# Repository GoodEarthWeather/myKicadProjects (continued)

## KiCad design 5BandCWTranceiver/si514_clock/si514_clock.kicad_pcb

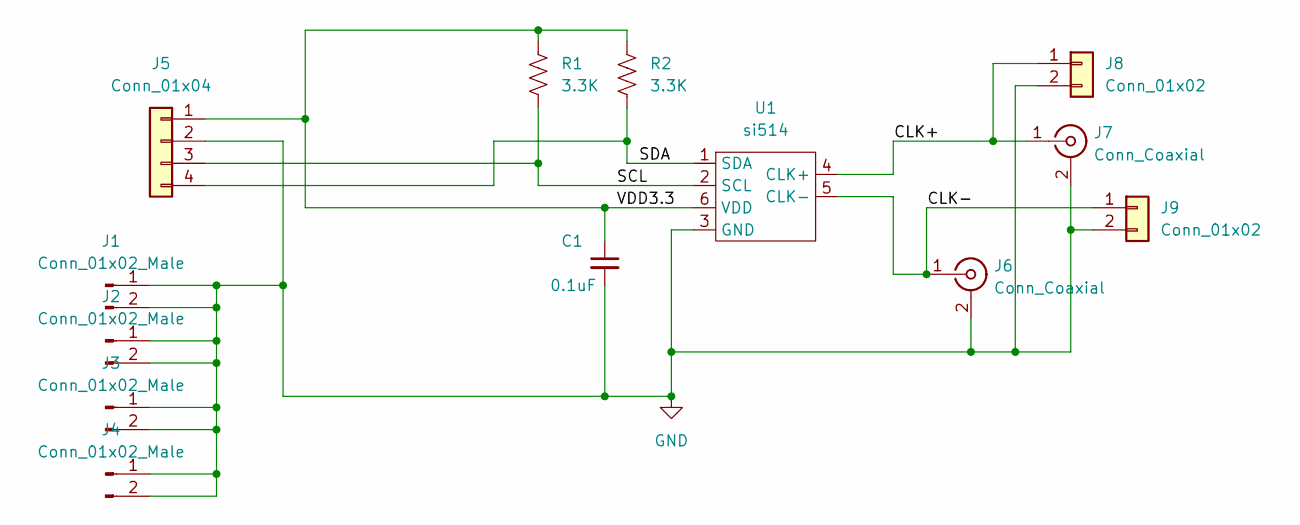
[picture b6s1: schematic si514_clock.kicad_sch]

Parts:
C1: 0.1uF; C_0603_1608Metric_Pad1.08x0.95mm_HandSolder
J1, J2, J3, J4: Conn_01x02_Male; PinHeader_1x02_P2.54mm_Vertical
J5: Conn_01x04; PinHeader_1x04_P2.54mm_Vertical
J6, J7: Conn_Coaxial; SMA_Samtec_SMA-J-P-X-ST-EM1_EdgeMount
J8, J9: Conn_01x02; PinHeader_1x02_P2.54mm_Vertical
R1, R2: 3.3K; R_0603_1608Metric_Pad0.98x0.95mm_HandSolder
U1: si514; si514_3.2x5

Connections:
/CLK+: J7.1 (In), J8.1, U1.4 (CLK+)
/CLK-: J6.1 (In), J9.1, U1.5 (CLK-)
/SCL: J5.3, R1.2, U1.2 (SCL)
/SDA: J5.4, R2.2, U1.1 (SDA)
/VDD3.3: C1.1, J5.1, R1.1, R2.1, U1.6 (VDD)
GND: C1.2, J1.1, J1.2, J2.1, J2.2, J3.1, J3.2, J4.1, J4.2, J5.2, J6.2 (Ext), J7.2 (Ext), J8.2, J9.2, U1.3 (GND)

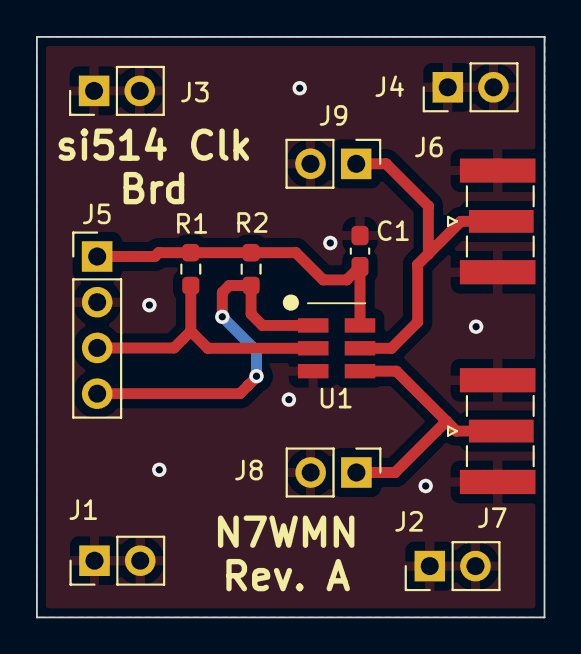
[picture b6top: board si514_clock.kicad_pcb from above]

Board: 2 copper layers, 28.2 x 32.2 mm, 13 parts (0 on the bottom side), 6 nets.

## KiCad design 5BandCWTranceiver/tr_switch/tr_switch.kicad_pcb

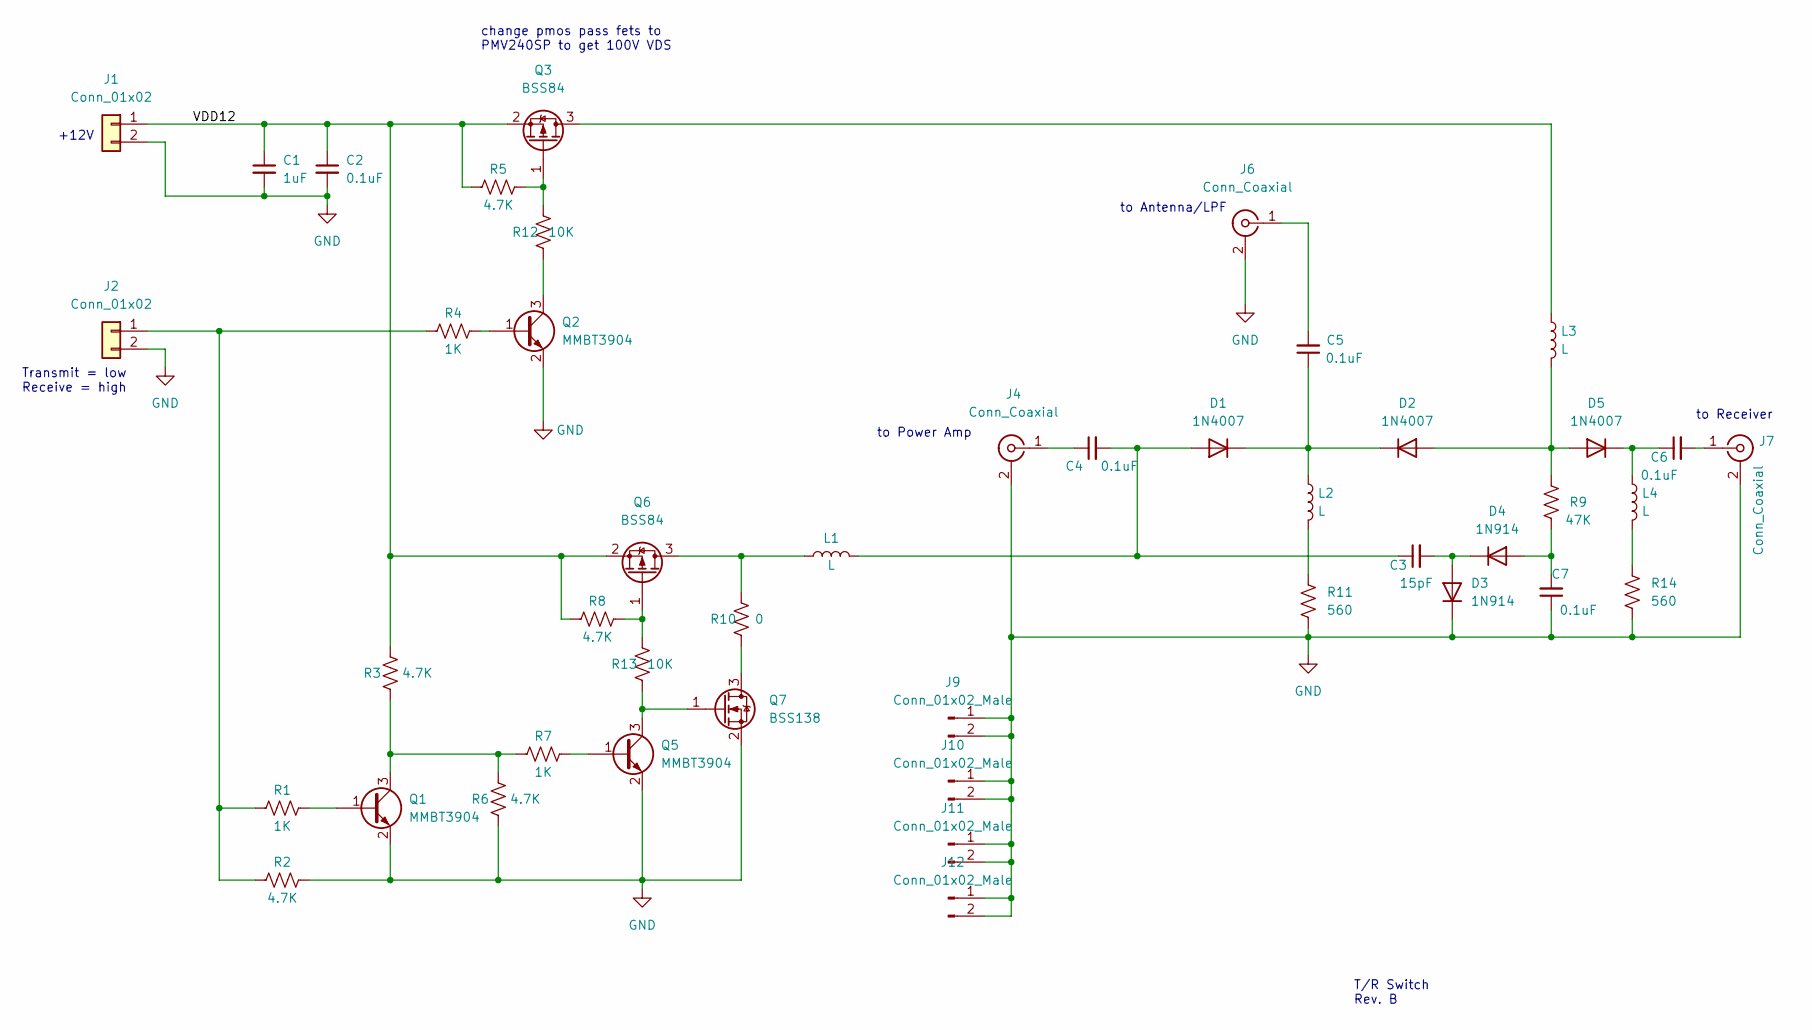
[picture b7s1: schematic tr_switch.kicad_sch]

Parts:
C1: 1uF; C_0603_1608Metric_Pad1.08x0.95mm_HandSolder
C2: 0.1uF; C_0603_1608Metric_Pad1.08x0.95mm_HandSolder
C3: 15pF; C_Disc_D5.0mm_W2.5mm_P5.00mm
C4, C5, C6, C7: 0.1uF; C_Disc_D5.0mm_W2.5mm_P5.00mm
D1, D2, D5: 1N4007; D_DO-41_SOD81_P10.16mm_Horizontal
D3, D4: 1N914; D_DO-35_SOD27_P7.62mm_Horizontal
J1, J2: Conn_01x02; PinHeader_1x02_P2.54mm_Vertical
J4, J6, J7: Conn_Coaxial; SMA_Samtec_SMA-J-P-X-ST-EM1_EdgeMount
J9, J10, J11, J12: Conn_01x02_Male; PinHeader_1x02_P2.54mm_Vertical
L1, L2, L3, L4: L; L_Toroid_Vertical_L10.0mm_W5.0mm_P5.08mm
Q1, Q2, Q5: MMBT3904; SOT-23
Q3, Q6: BSS84; SOT-23
Q7: BSS138; SOT-23
R1, R4, R7: 1K; R_0603_1608Metric_Pad0.98x0.95mm_HandSolder
R2, R3, R5, R6, R8: 4.7K; R_0603_1608Metric_Pad0.98x0.95mm_HandSolder
R9: 47K; R_0603_1608Metric_Pad0.98x0.95mm_HandSolder
R10: 0; R_0603_1608Metric_Pad0.98x0.95mm_HandSolder
R11, R14: 560; R_Axial_DIN0411_L9.9mm_D3.6mm_P15.24mm_Horizontal
R12, R13: 10K; R_0603_1608Metric_Pad0.98x0.95mm_HandSolder

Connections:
/VDD12: C1.1, C2.1, J1.1, Q3.2 (S), Q6.2 (S), R3.2, R5.1, R8.1
GND: C1.2, C2.2, C7.1, D3.1 (K), J1.2, J2.2, J4.2 (Ext), J6.2 (Ext), J7.2 (Ext), J9.1, J9.2, J10.1, J10.2, J11.1, J11.2, J12.1, J12.2, Q1.2 (E), Q2.2 (E), Q5.2 (E), Q7.2 (S), R2.1, R6.1, R11.2, R14.2
unnamed: C3.1, C4.2, D1.2 (A), L1.2
unnamed: C3.2, D3.2 (A), D4.1 (K)
unnamed: C4.1, J4.1 (In)
unnamed: C5.1, D1.1 (K), D2.1 (K), L2.1
unnamed: C5.2, J6.1 (In)
unnamed: C6.1, D5.1 (K), L4.1
unnamed: C6.2, J7.1 (In)
unnamed: C7.2, D4.2 (A), R9.1
unnamed: D2.2 (A), D5.2 (A), L3.2, R9.2
unnamed: J2.1, R1.1, R2.2, R4.1
unnamed: L1.1, Q6.3 (D), R10.2
unnamed: L2.2, R11.1
unnamed: L3.1, Q3.3 (D)
unnamed: L4.2, R14.1
unnamed: Q1.1 (B), R1.2
unnamed: Q1.3 (C), R3.1, R6.2, R7.1
unnamed: Q2.1 (B), R4.2
unnamed: Q2.3 (C), R12.1
unnamed: Q3.1 (G), R5.2, R12.2
unnamed: Q5.1 (B), R7.2
unnamed: Q5.3 (C), Q7.1 (G), R13.1
unnamed: Q6.1 (G), R8.2, R13.2
unnamed: Q7.3 (D), R10.1

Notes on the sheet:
T/R Switch Rev. B
+12V
Transmit = low Receive = high
to Receiver
to Power Amp
change pmos pass fets to PMV240SP to get 100V VDS
to Antenna/LPF

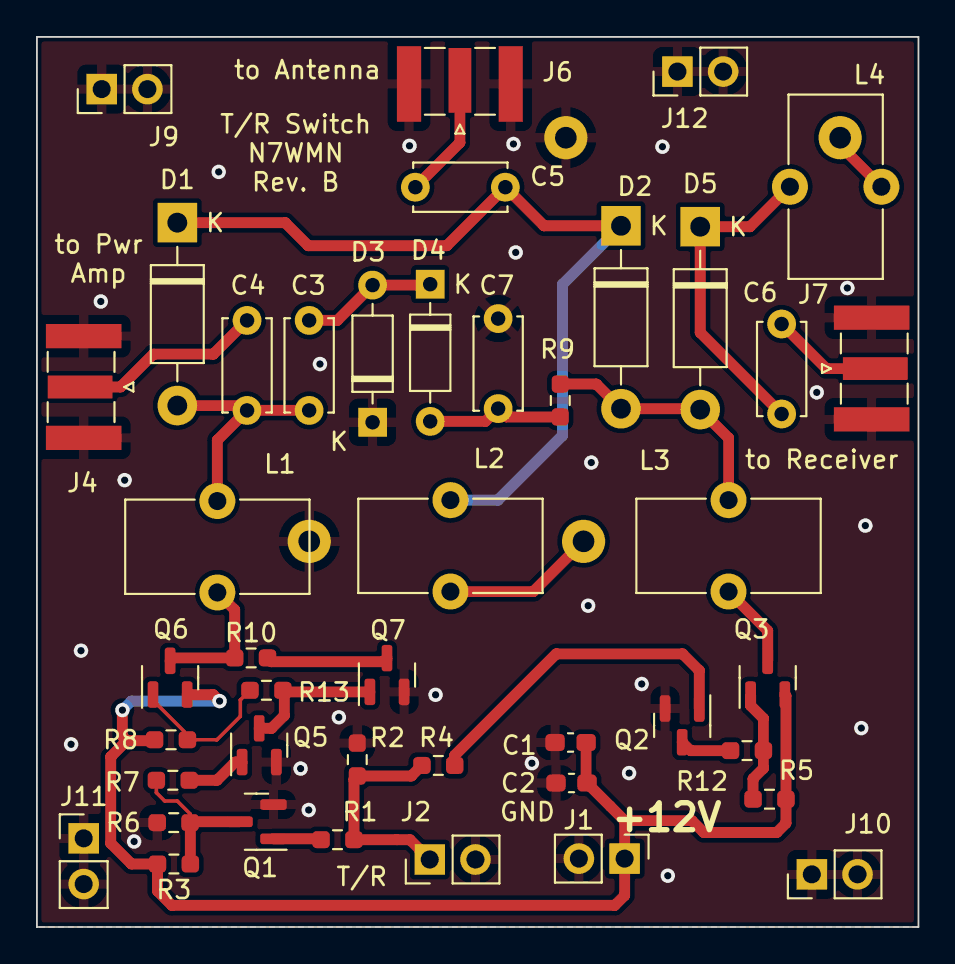
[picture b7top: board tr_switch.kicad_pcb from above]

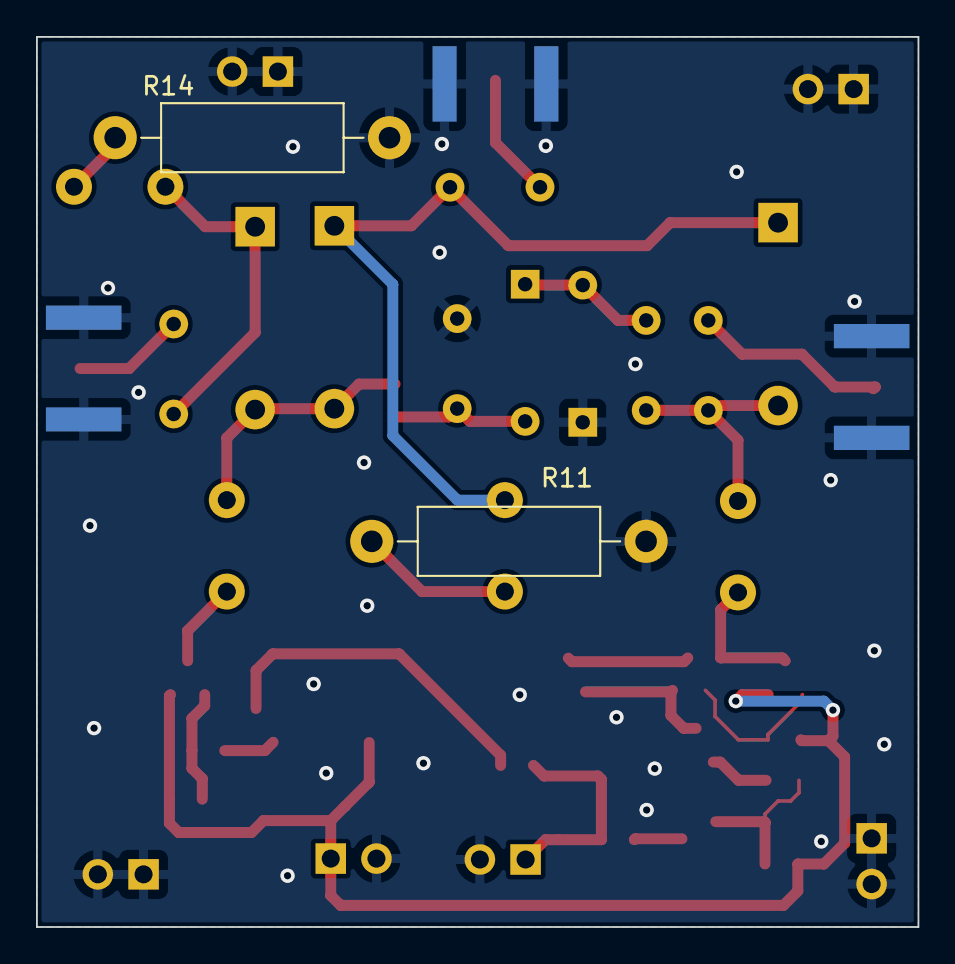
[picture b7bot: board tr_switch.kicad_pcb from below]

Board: 2 copper layers, 49.0 x 49.5 mm, 45 parts (2 on the bottom side), 25 nets.
